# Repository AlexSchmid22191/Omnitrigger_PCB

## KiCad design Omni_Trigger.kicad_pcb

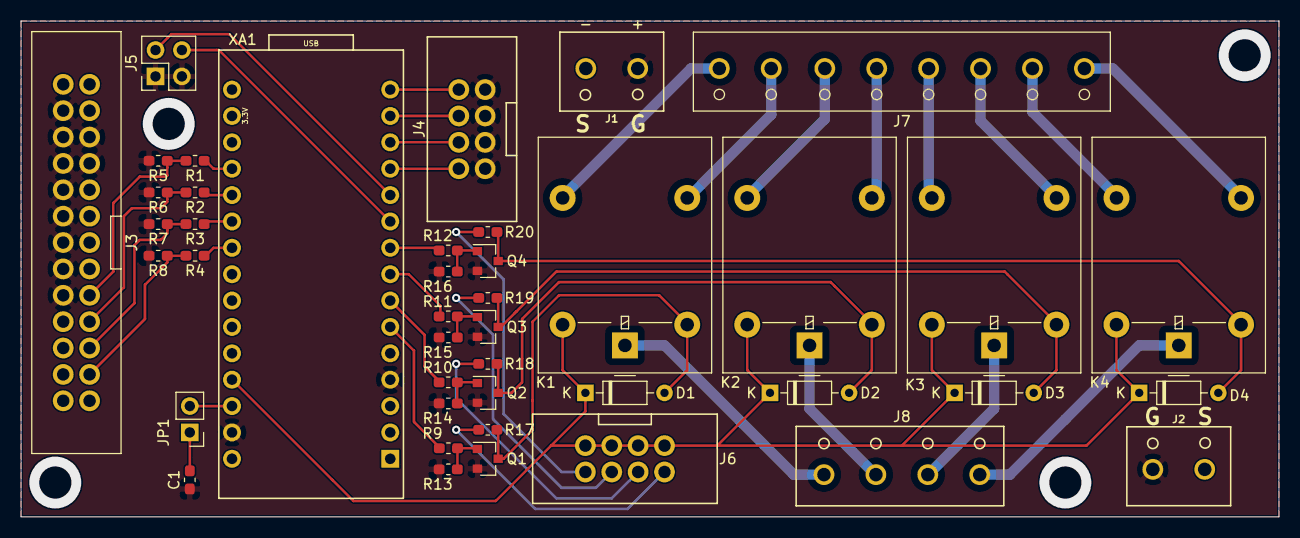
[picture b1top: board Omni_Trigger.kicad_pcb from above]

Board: 2 copper layers, 121.2 x 47.8 mm, 43 parts (0 on the bottom side), 47 nets.

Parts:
C1: C_Small; C_0603_1608Metric_Pad1.05x0.95mm_HandSolder
D1, D2, D3, D4: 1N4148; D_DO-35_SOD27_P7.62mm_Horizontal
J1, J2: Screw_Terminal_01x02; RS_Screw_Term_x2
J3: Conn_02x13_Top_Bottom; IDC_13x02_Sided
J4, J6: Conn_02x04_Odd_Even; IDC_04x02
J5: Conn_02x02_Odd_Even; PinHeader_2x02_P2.54mm_Vertical
J7: Screw_Terminal_01x08; RS_Screw_Term_x8
J8: Screw_Terminal_01x04; RS_Screw_Term_x4
JP1: Jumper_2_Open; PinHeader_1x02_P2.54mm_Vertical
K1, K2, K3, K4: G5LE-1; Relay_SPDT_Omron-G5LE-1
Q1, Q2, Q3, Q4: BS170F; SOT-23
R1, R2, R3, R4, R5, R6, R7, R8, R9, R10, R11, R12, R13, R14, R15, R16, R17, R18, R19, R20: R; R_0603_1608Metric_Pad1.05x0.95mm_HandSolder
XA1: Arduino_Nano_Socket

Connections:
+5V: D1.1, D2.1, D3.1, D4.1, J6.1, J6.3, J6.5, J6.7, K1.5, K2.5, K3.5, K4.5, XA1.5V
/Shield: J1.2, J2.2
GND: C1.2, J1.1, J2.1, J3.10, J3.11, J3.18, J3.19, J3.20, J3.21, J3.22, J3.23, J3.24, J3.25, J4.1, J4.3, J4.5, J4.7, J5.1, J5.3, Q1.2, Q2.2, Q3.2, Q4.2, R5.2, R6.2, R7.2, R8.2, R13.2, R14.2, R15.2, R16.2, XA1.GND1, XA1.GND2
unnamed: C1.1, JP1.1
unnamed: D1.2, K1.2, Q1.3, R17.2
unnamed: D2.2, K2.2, Q2.3, R18.2
unnamed: D3.2, K3.2, Q3.3, R19.2
unnamed: D4.2, K4.2, Q4.3, R20.2
unnamed: J3.2, R4.2, R8.1
unnamed: J3.3, R3.2, R7.1
unnamed: J3.4, R2.2, R6.1
unnamed: J3.5, R1.2, R5.1
unnamed: J4.2, XA1.D9
unnamed: J4.4, XA1.D10
unnamed: J4.6, XA1.D11
unnamed: J4.8, XA1.D12
unnamed: J5.2, XA1.D8
unnamed: J5.4, XA1.D7
unnamed: J6.2, R17.1
unnamed: J6.4, R18.1
unnamed: J6.6, R19.1
unnamed: J6.8, R20.1
unnamed: J7.1, K4.3
unnamed: J7.2, K4.4
unnamed: J7.3, K3.3
unnamed: J7.4, K3.4
unnamed: J7.5, K2.3
unnamed: J7.6, K2.4
unnamed: J7.7, K1.3
unnamed: J7.8, K1.4
unnamed: J8.1, K1.1
unnamed: J8.2, K2.1
unnamed: J8.3, K3.1
unnamed: J8.4, K4.1
unnamed: JP1.2, XA1.RST2
unnamed: Q1.1, R9.2, R13.1
unnamed: Q2.1, R10.2, R14.1
unnamed: Q3.1, R11.2, R15.1
unnamed: Q4.1, R12.2, R16.1
unnamed: R1.1, XA1.A0
unnamed: R2.1, XA1.A1
unnamed: R3.1, XA1.A2
unnamed: R4.1, XA1.A3
unnamed: R9.1, XA1.D3
unnamed: R10.1, XA1.D4
unnamed: R11.1, XA1.D5
unnamed: R12.1, XA1.D6

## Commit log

2020-05-30 Removed unneeded mounting holes in the Nano Footprint
2020-09-17 Redrew Board in Stablöe Kicad for compatibility
2020-09-18 Made ground connection to shield plane available at screw terminals
2020-09-30 Updated clearances
